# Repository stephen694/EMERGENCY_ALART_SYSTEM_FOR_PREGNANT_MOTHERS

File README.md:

Julius-branch
# Emergency Alert System for Pregnant Mothers in Kenya

> *Saving Lives with One Button — Fast, Simple, Reliable Maternal Emergency Alerts*

# Quick Links

- [Project Report (Final)](./Emergency_Alert_System_Final_Report.docx)
- [Circuit Schematic (Fritzing / EasyEDA)](./doc/schematic/)
- [Firmware Source Code](./src/)
- [Deployment & Field Testing Notes](./doc/deployment.md)

# Emergency Alert System on Arduino

This project brings a one-button maternal emergency alert device to life using the Arduino Uno platform. It allows a pregnant woman — with no smartphone, no internet, and no need to speak — to dispatch an SMS alert containing her real-time GPS location to pre-registered healthcare contacts with a single button press.

The system leverages Kenya's existing GSM mobile network infrastructure (Safaricom, Airtel, Telkom) and is designed to complement the [m-mama](https://www.mobilematernityafrica.org/) emergency transport system. Its low-power design supports both USB and solar charging, making it suitable for off-grid rural Kenyan communities.

# Contents

- Installation & Setup:
  - [Hardware Assembly](#hardware-assembly)
  - [Uploading Firmware via Arduino IDE](#uploading-firmware-via-arduino-ide)
  - [Configuring Emergency Contacts](#configuring-emergency-contacts)
  - [Power Options](#power-options)
- [How It Works](#how-it-works)
- [System Architecture](#system-architecture)
- [Components & Libraries](#components--libraries)
- [Documentation](#documentation)
- [Issues and Support](#issues-and-support)
- [Contributing](#contributing)
- [License and Credits](#license-and-credits)

---

## Hardware Assembly

The following components are required to assemble the device:

| Component | Specification |
|-----------|--------------|
| Microcontroller | Arduino Uno |
| GSM Module | SIM800L or SIM900 |
| GPS Module | Neo-6M |
| Display | 16x2 LCD |
| User Input | Physical Push Button |
| Audio Feedback | 5V Buzzer |
| Power | USB or Solar-compatible stable supply |

Refer to the circuit schematic in [`/doc/schematic/`](./doc/schematic/) for wiring diagrams produced in Fritzing and EasyEDA.

1. Wire the **Neo-6M GPS module** to the Arduino using SoftwareSerial pins (D2/D3).
2. Wire the **SIM800L/SIM900 GSM module** to the Arduino using SoftwareSerial pins (D7/D8). Ensure the GSM module has its own stable power supply (3.4–4.2V for SIM800L) to handle peak current draw.
3. Connect the **16x2 LCD** via I2C (SDA/SCL) or direct 4-bit parallel wiring to digital pins.
4. Connect the **push button** to digital pin D4 with a pull-down resistor.
5. Connect the **buzzer** to digital pin D5.

---

## Uploading Firmware via Arduino IDE

1. [Download and install the Arduino IDE](https://www.arduino.cc/en/software) (v1.x or v2.x).
2. Clone or download this repository.
3. Open `src/emergency_alert/emergency_alert.ino` in the Arduino IDE.
4. Install the required libraries via **Tools > Manage Libraries**:
   - **TinyGPS++** by Mikal Hart
   - **SoftwareSerial** (included with Arduino IDE)
   - **LiquidCrystal** or **LiquidCrystal_I2C** (depending on LCD wiring)
5. Select **Tools > Board > Arduino Uno**.
6. Select the correct COM port under **Tools > Port**.
7. Click **Upload**.

---

## Configuring Emergency Contacts

Pre-registered healthcare contact numbers are set in the firmware before upload. Open `src/emergency_alert/config.h` and edit the following:

```cpp
// Add up to 5 pre-registered emergency contact numbers
const char* EMERGENCY_CONTACTS[] = {
  "+254XXXXXXXXX",   // Primary healthcare contact
  "+254XXXXXXXXX",   // Secondary contact (midwife / CHW)
};
const int NUM_CONTACTS = 2;
```

The outgoing SMS will be sent to all listed numbers simultaneously.

---

## Power Options

The device supports two charging modes:

- **USB Charging** — Connect to any USB 5V power source or power bank.
- **Solar Charging** — A solar panel with a 5V regulator can be connected to the USB input for off-grid operation. Recommended for field deployment in rural settings without reliable grid access.

The LCD displays a low-battery warning when charge drops to critical levels.

---

## How It Works

1. The user **presses and holds** the emergency button for **3 seconds**.
2. The LCD prompts: *"Press again to confirm"* — preventing false activations.
3. The Arduino queries the **Neo-6M GPS module** for current coordinates.
   - GPS lock available → coordinates formatted as a **Google Maps URL**.
   - GPS lock unavailable → last known coordinates used, or *"Location Unavailable"* noted in SMS.
4. The **SIM800L/SIM900 GSM module** transmits the SMS to all pre-registered contacts.
5. If delivery fails, **automatic retry logic** re-attempts transmission.
6. The LCD displays: *"Alert Sent — Help Coming"* (English and Swahili).
7. The buzzer sounds for audible confirmation.

### SMS Format

```
EMERGENCY: Pregnant woman needs help.
Msaada: Mwanamke mjamzito anahitaji msaada.
Location: https://maps.google.com/?q=-1.2345,36.8765
Time: 2025-06-01 14:32:07
```

---

## System Architecture

```
[Button Hold 3s]
      │
      ▼
[Arduino Uno] ──► [Neo-6M GPS Module] ──► Fetch coordinates
      │
      ├──► Format Google Maps URL
      │
      ├──► [SIM800L/SIM900 GSM Module] ──► Send SMS → pre-registered contacts
      │                                        │
      │                                   [Retry if undelivered]
      │
      └──► [16x2 LCD + Buzzer] ──► Confirm to user
```

---

## Components & Libraries

### Hardware

| Component | Purpose |
|-----------|---------|
| Arduino Uno | Main microcontroller — coordinates all operations |
| SIM800L / SIM900 | SMS transmission over GSM without internet |
| Neo-6M GPS | Real-time geographic coordinate capture |
| Push Button | Single user input; 3s hold-to-confirm |
| 16x2 LCD | Confirmation messages (English & Swahili) |
| Buzzer | Audible alert confirmation |
| Stable Power Supply | USB + solar compatible; low-power design |

### Software & Libraries

| Library / Tool | Purpose |
|----------------|---------|
| Arduino IDE | Firmware development and upload |
| TinyGPS++ | Parses NMEA sentences from Neo-6M GPS |
| SoftwareSerial | Serial comms between Arduino, GPS, and GSM modules |
| LiquidCrystal / LiquidCrystal_I2C | LCD display control |
| Google Maps URL | Formats GPS coordinates as a clickable link in SMS |
| Fritzing / EasyEDA | Circuit schematic and PCB layout documentation |

---

## Documentation

Full project documentation is located in the [`/doc`](./doc/) directory and includes:

- Circuit schematics and PCB layout files
- Component datasheets
- Deployment field notes and testing logs
- User manual (English and Swahili)

The final project report covering problem statement, risk analysis, competitive landscape, and future work is available at the root of this repository: [`Emergency_Alert_System_Final_Report.docx`](./Emergency_Alert_System_Final_Report.docx).

---

## Issues and Support

If you encounter a bug or want to propose an enhancement, please [open an issue](../../issues) on GitHub.

When submitting an issue, please include:

- Arduino IDE version and board settings
- Sketch code (wrapped in a code block)
- Serial Monitor output at the time of the problem
- GSM module model and SIM network (Safaricom / Airtel / Telkom)
- GPS module model and whether testing was indoors or outdoors
- Battery/power supply configuration

For general questions about hardware assembly, deployment in the field, or community health worker training, please open a [Discussion](../../discussions).

---

## Contributing

For minor fixes to code or documentation, go ahead and submit a pull request.

For larger changes — new features, sensor additions, PCB redesigns, or new language support on the LCD — please open an issue first to discuss the approach before submitting a PR.

This project uses a **feature-branch workflow**:

- Work on a dedicated branch: e.g., `feature/solar-charging`, `feature/swahili-lcd`
- Submit a pull request for peer review before merging into `main`
- `main` always contains stable, tested code
- Use `hotfix/` branches for urgent bug fixes found during field testing
- Please squash small or iterative commits before opening a pull request

---

## License and Credits

This project is licensed under the [MIT License](./LICENSE).

**Project Team:**

| Name | Role |
|------|------|
| Stephen Ngige | Firmware development, Proteus simulation, debugging |
| Ham Thoya | Component selection, electrical design, SMS verification, performance validation |
| Julius Mwangi | Mechanical design, technical documentation |

**Third-Party Libraries:**

- [TinyGPS++](https://github.com/mikalhart/TinyGPSPlus) by Mikal Hart — licensed under LGPL v2.1
- [SoftwareSerial](https://github.com/plerup/espsoftwareserial) — included with the Arduino IDE
- [LiquidCrystal_I2C](https://github.com/johnrickman/LiquidCrystal_I2C) by Frank de Brabander — licensed under GPL v3

**Related Projects & Inspiration:**

- [m-mama Emergency Transport System](https://www.mobilematernityafrica.org/) — complementary dispatch infrastructure this device is designed to integrate with
- [Arduino](https://www.arduino.cc/) — the open-source hardware and software platform this project is built on

---

*Designed specifically for the Kenyan context — leveraging existing GSM infrastructure to address a life-critical communication gap for pregnant women in rural and semi-urban Kenya.*
# EMERGENCY_ALART_SYSTEM_FOR_PREGNANT_MOTHERS

## Collaborators
1. Masika: Supervisor
2. main

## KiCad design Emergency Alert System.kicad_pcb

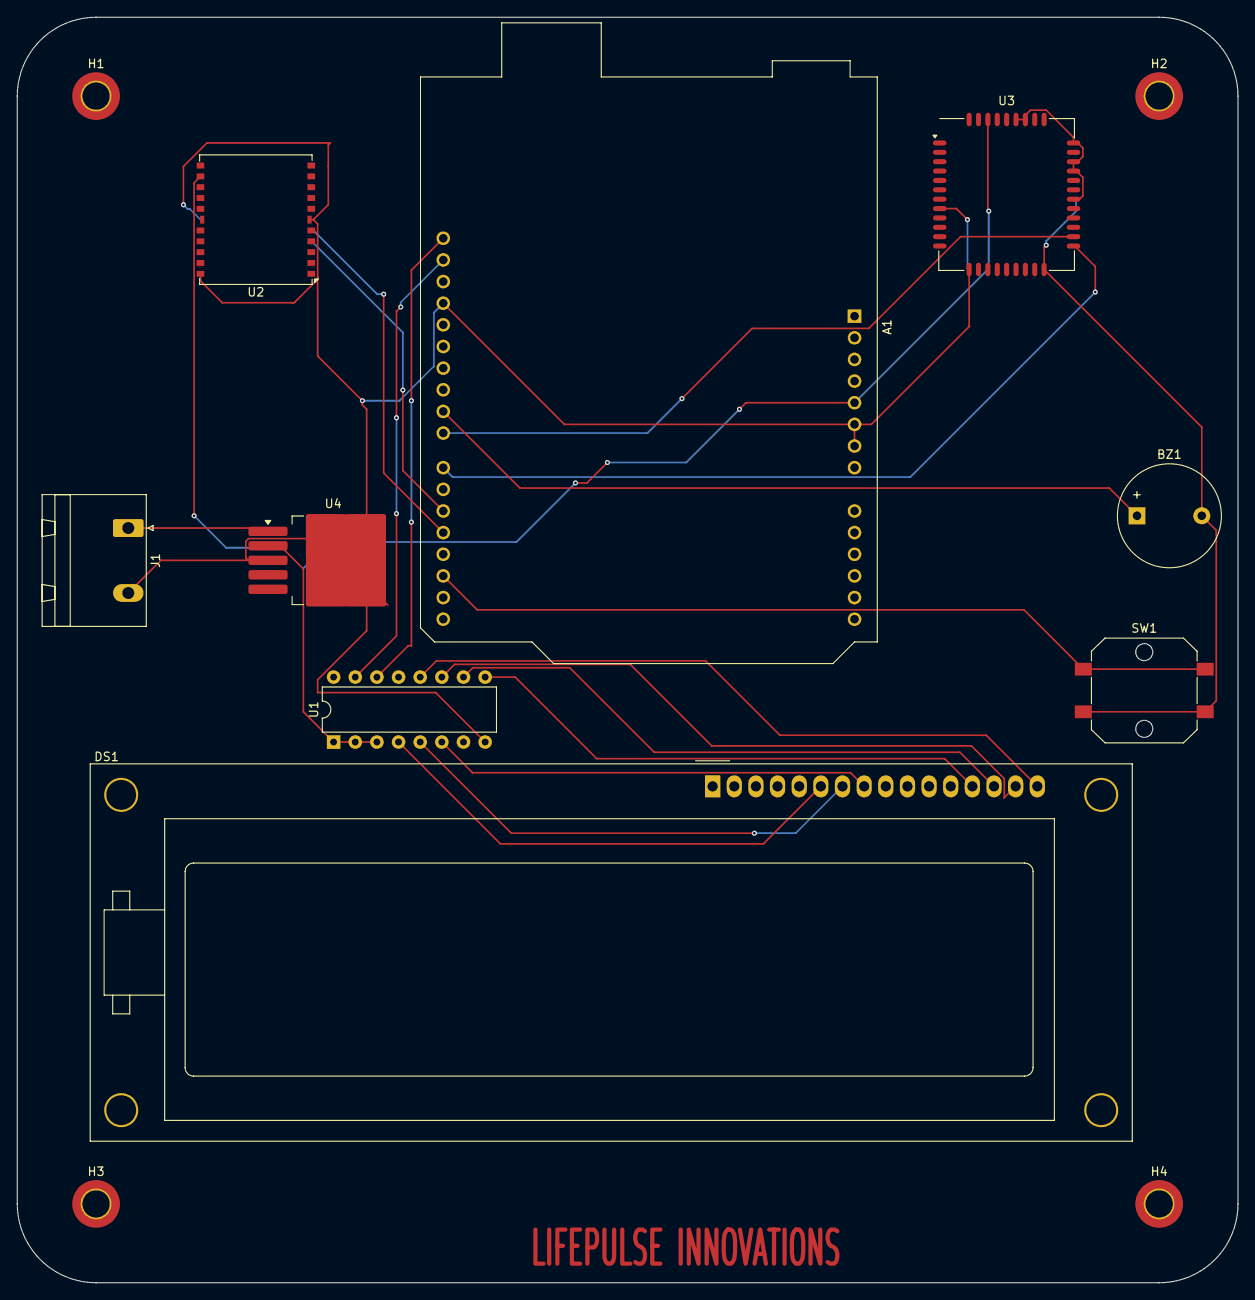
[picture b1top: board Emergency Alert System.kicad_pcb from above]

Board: 2 copper layers, 143.2 x 148.5 mm, 13 parts (0 on the bottom side), 18 nets.

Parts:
A1: Arduino_UNO_R3
BZ1: Buzzer; Buzzer_12x9.5RM7.6
DS1: HY1602E
H1, H2, H3, H4: MountingHole_Pad; MountingHole_3.2mm_M3_DIN965_Pad_TopBottom
J1: Conn_01x02_Pin; PhoenixContact_GMSTBA_2,5_2-G-7,62_1x02_P7.62mm_Horizontal
SW1: SW_Push; SW_Push_1P1T_NO_CK_PTS125Sx43PSMTR
U1: PCF8574AP; DIP-16_W7.62mm
U2: RXM-GPS-RM; Linx_RXM-GPS
U3: SIM800C; SIMCom_SIM800C
U4: LM2596S-3.3; TO-263-5_TabPin3

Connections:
+5V: A1.5 (+5V), U1.1 (A0), U1.2 (A1), U1.3 (A2), U2.12 (VCC), U3.40 (VDD_EXT), U4.2 (OUT)
/BZ: A1.24 (D9), BZ1.1 (+)
/D4: DS1.13 (DB4), U1.9 (P4)
/D5: DS1.14 (DB5), U1.10 (P5)
/D6: DS1.15 (DB6), U1.11 (P6)
/D7: DS1.16 (DB7), U1.12 (P7)
/E: DS1.8 (E), U1.6 (P2)
/GPSRX: A1.19 (D4), U2.5 (RX)
/GPSTX: A1.20 (D5), U2.4 (TX)
/GSMRX: A1.23 (D8), U3.23 (UART2_RXD)
/GSMTX: A1.22 (D7), U3.22 (UART2_TXD)
/PB: A1.17 (D2), SW1.1
/RS: DS1.6 (RS), U1.4 (P0)
/R/W: DS1.7 (R/~W), U1.5 (P1)
/SCL: A1.32 (SCL/A5), U1.14 (SCL)
/SDA: A1.31 (SDA/A4), U1.15 (SDA)
Earth: A1.6 (GND), A1.7 (GND), A1.29 (GND), BZ1.2 (-), J1.2, SW1.2, U1.8 (GND), U2.18 (GND), U2.20 (GND), U2.21 (GND), U2.22 (GND), U3.8 (GND), U3.13 (GND), U3.19 (GND), U3.21 (GND), U3.27 (GND), U3.30 (GND), U3.31 (GND), U3.33 (GND), U3.36 (GND), U3.37 (GND), U4.3 (GND)
unnamed: J1.1, U4.1 (VIN)
